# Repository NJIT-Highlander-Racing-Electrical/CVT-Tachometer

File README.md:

# CVT-Tachometer

A subsystem that measures the RPM of the primary and secondary on the CVT. This subsystem also has a temperature sensor to detect if the CVT is overheating.

## 2024-2025 Design Goals

* Everything last year seemed to work well, but a few improvements to the existing system could be made:
  * Software
       * Improve program to do more analog reads and spend less time processing data
          * This may involve constants that are only calculated once during setup, faster math functions, fewer delays, etc
       * Use the analog reads for IR sensors on both ADC1 and ADC2 to prevent any issues. 
  * Sensor Enclosures
       * the sensor housings should be made out of something other than PLA
       * they should be able to fit custom PCBs with connectors
       * the hood around the emitter and receiver should be enlarged to prevent anything else from reflecting other than what is directly in front
  * PCBs for sensors
       * the wiring from the sensors to the main electronics housing were tough to do
       * A small PCB for the electronics would be nicer than hand soldering wires
       * A connector would also be good so that they can be removed/swapped easily
            * Maybe 1x4 or 1x5 or 1x6 JST depending on how many conductors we need going to each board
  * Additional TMP36 Sensor
      * Another TMP36 temperature sensor can be added so that there is only one version of the sensor PCB, and we get a better idea of the temperature gradient within the CVT case (primary vs secondary).
  * Additional Note
     * On the IR receiver output, have it split to two GPIO. One leg has a potentiometer (0-10k?) between the output and the GPIO for finding the optimal resistance. Also make sure it has a small series resistor to prevent resistance from dropping completely to zero. The other GPIO has a fixed resistor that can be added after the fact that will be used in the long term. 

## Hardware Components:

* IR Sensors that point at primary and secondary.
- These can detect when a white stripe on the CVT passes by (one revolution)
* Microcontroller to convert the number of revolutions per second into an RPM value for dashboard and DAS (via CAN-Bus)
  - Uses ESP32 and TJA1051T CAN-Bus transceiver
* TMP36 Temperature Sensor to look at ambient temperature in the CVT case
- Sends a bit via CAN-Bus to turn on an overheating status LED on the dashboard

 ## Notes

 * Super-Bright IR LEDs support an output current of 100mA with a forward voltage of 1.6V. This means a voltage drop of 5V-1.6V = 3.4V across the 1W resistor. To achieve a current of roughly 75mA, we are using a 47 ohm resistor
    * 5V -> IR LED -> Resistor -> Ground
 * Using standard infrared photodiodes, we can simply power the IR leds without needing a 38kHz pulse rate
    * 5V -> IR Diode -> Resistor -> Ground (sample signal between diode and resistor voltage divider)
 * Temperature sensor is TMP36
    * 5V - > TMP36 VCC, GND -> TMP 36 GND, VOUT -> GPIO
 * Connections from the LEDs/sensors to the main body should be sealed/waterproof
 * The holes in the CVT case should be 20mm
 * The infrared diode appears to act like a variable resistor, but voltage polarity must be + on cathode (short negative leg) and - on anode (short positive leg)

 * The software utilizes the dual core functionality of the ESP32
   * Core 1 reads primaryRPM and deals with CAN-Bus communication
      * It is very important that all other processing is kept to a minimum to ensure primaryRPM is accurately read
   * Core 0 solely reads secondaryRPM

### Previous Issues 
 * One issue noticed during the testing phase was that the analog sensor readings were constantly peaking (4095). The resistor divider for the IR receivers needed to be adjusted to roughly 2700 ohms
 * It looked like the analog readings were having issues at comp too. It was either 0-3 ish mph or 41
     * This has been solved on 9/18/24 with dynamically adjusting analog thresholds
 * Analog reads are not ideal for this type of data acquisition. Fast readings are needed, and there should be no margin for error about whether a reading falls within a range
 * Digital readings with a hall sensor, engine spark plug with octocoupler, or some other digital signal could be implemented 

## Electrical Wiring Notes

### Pins to sensor modules

* Pin 1: +5V
* Pin 2: GND
* Pin 3: TMP36 Output
* Pin 4: IR Emitter Return Line
* Pin 5: IR Receiver Return Line

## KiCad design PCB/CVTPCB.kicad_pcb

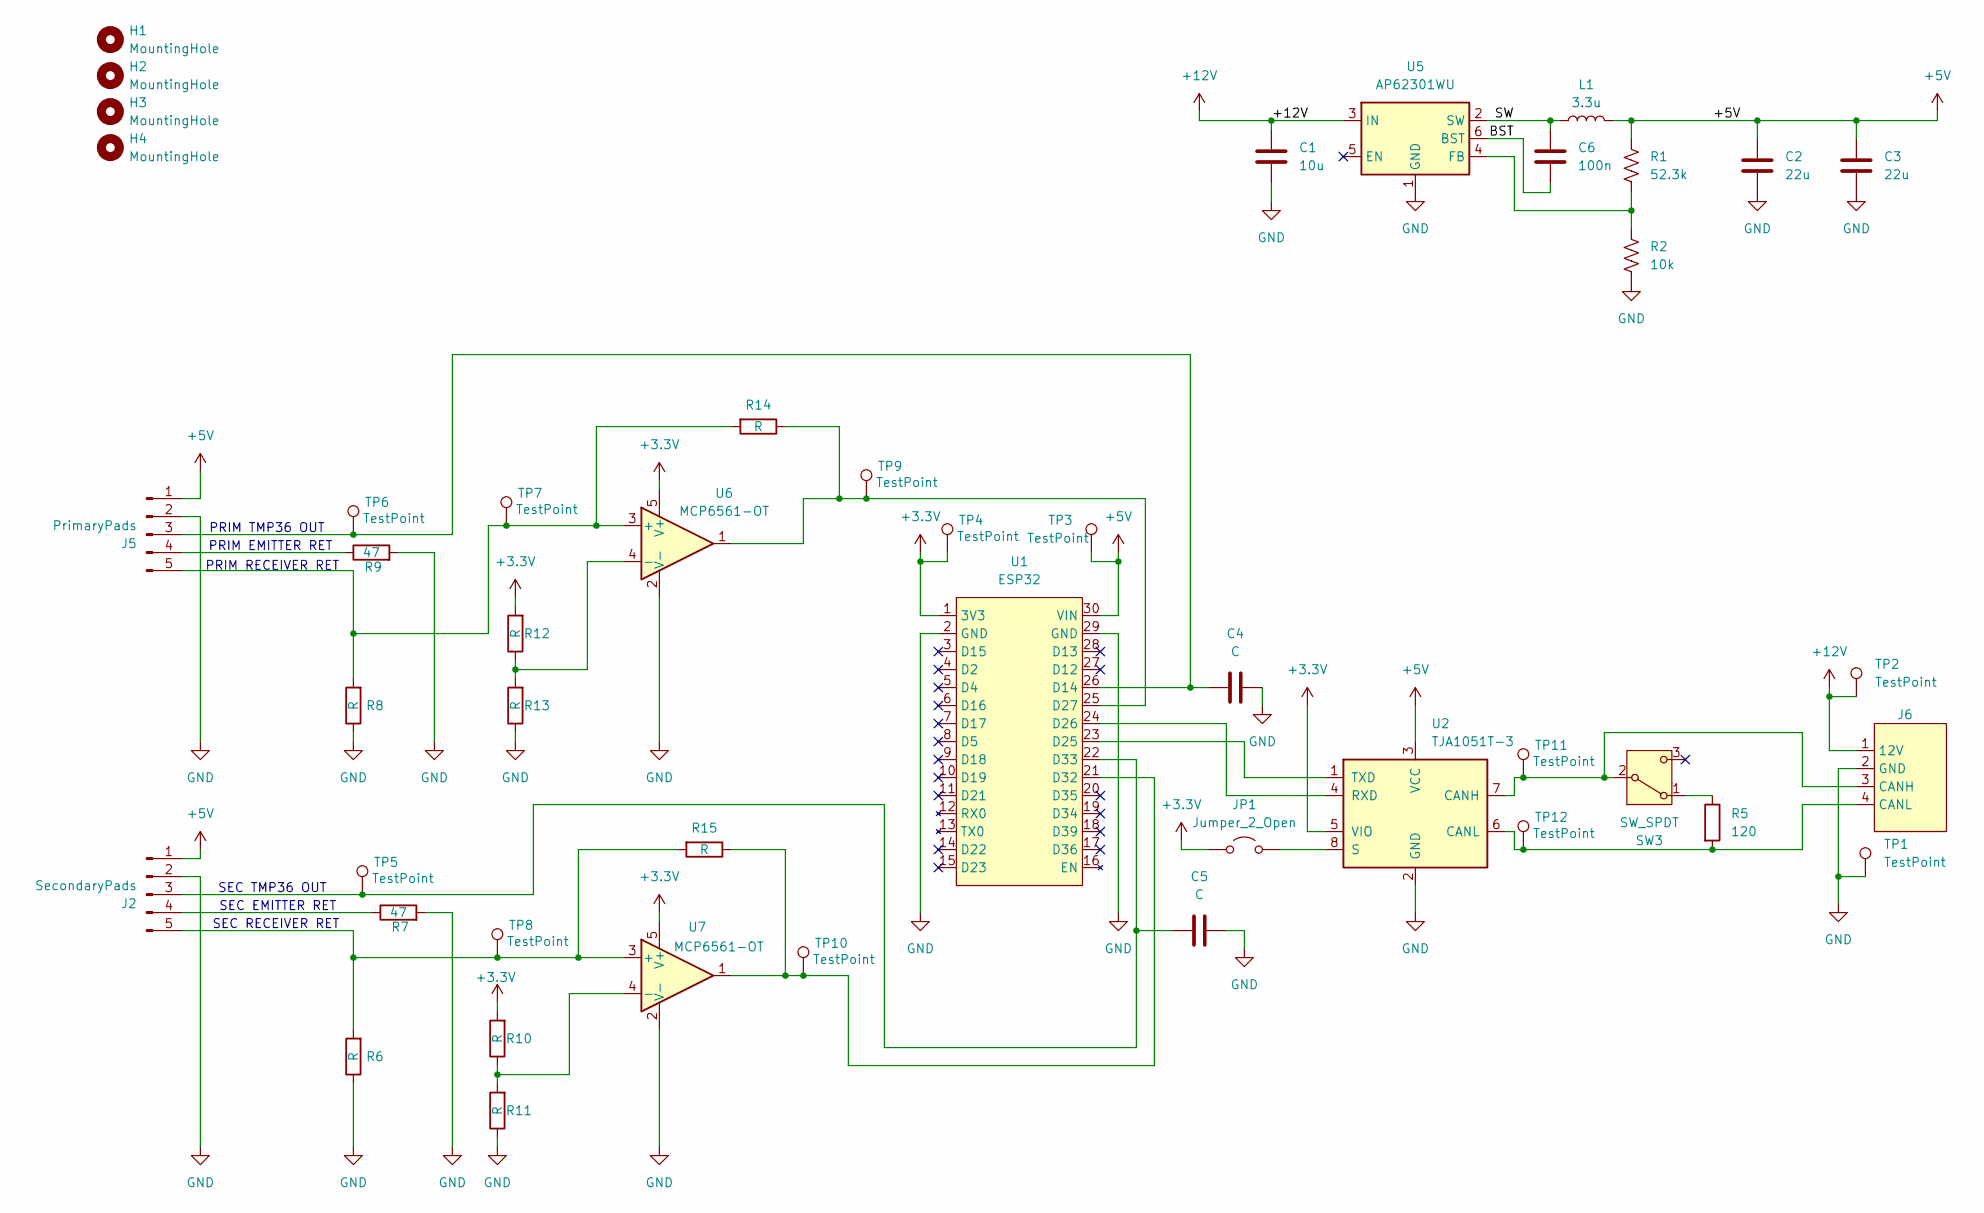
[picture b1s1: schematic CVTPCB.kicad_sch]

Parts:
C1: 10u; C_0805_2012Metric_Pad1.18x1.45mm_HandSolder
C2, C3: 22u; C_0603_1608Metric_Pad1.08x0.95mm_HandSolder
C4, C5: C; C_0805_2012Metric_Pad1.18x1.45mm_HandSolder
C6: 100n; C_0402_1005Metric_Pad0.74x0.62mm_HandSolder
H1, H2, H3, H4: MountingHole; MountingHole_4.3mm_M4
J2: SecondaryPads; Temp_IR_5_Pad_Combo
J5: PrimaryPads; Temp_IR_5_Pad_Combo
J6: Aviation Plug Pads
JP1: Jumper_2_Open; SolderJumper-2_P1.3mm_Open_Pad1.0x1.5mm
L1: 3.3u; L_Taiyo-Yuden_NR-50xx
R1: 52.3k; R_0402_1005Metric
R2: 10k; R_0402_1005Metric
R5: 120; R_1206_3216Metric_Pad1.30x1.75mm_HandSolder
R6, R8, R10, R11, R12, R13, R14, R15: R; R_1206_3216Metric_Pad1.30x1.75mm_HandSolder
R7, R9: 47; R_Axial_DIN0411_L9.9mm_D3.6mm_P12.70mm_Horizontal
SW3: SW_SPDT; SW_SPDT_CK_JS102011SAQN
TP1, TP2, TP3, TP4, TP5, TP6, TP7, TP8, TP9, TP10, TP11, TP12: TestPoint; TestPoint_THTPad_D3.0mm_Drill1.5mm
U1: ESP32
U2: TJA1051T-3; SOIC-8_3.9x4.9mm_P1.27mm
U5: AP62301WU; TSOT-23-6
U6, U7: MCP6561-OT; SOT-23-5

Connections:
+3.3V: JP1.1 (A), R10.2, R12.2, TP4.1, U1.1 (3V3), U2.5 (VIO), U6.5 (V+), U7.5 (V+)
+5V: C2.1, C3.1, J2.1, J5.1, L1.2, R1.1, TP3.1, U1.30 (VIN), U2.3 (VCC)
+12V: C1.1, J6.1 (12V), TP2.1, U5.3 (IN)
/BST: C6.2, U5.6 (BST)
/SW: C6.1, L1.1, U5.2 (SW)
GND: C1.2, C2.2, C3.2, C4.2, C5.2, J2.2, J5.2, J6.2 (GND), R2.2, R6.1, R7.2, R8.1, R9.2, R11.1, R13.1, TP1.1, U1.2 (GND), U1.29 (GND), U2.2 (GND), U5.1 (GND), U6.2 (V-), U7.2 (V-)
unnamed: C5.1, J2.3, TP5.1, U1.22 (D33)
unnamed: J2.4, R7.1
unnamed: J2.5, R6.2, R15.2, TP8.1, U7.3 (+)
unnamed: C4.1, J5.3, TP6.1, U1.26 (D14)
unnamed: J5.4, R9.1
unnamed: J5.5, R8.2, R14.2, TP7.1, U6.3 (+)
unnamed: J6.3 (CANH), SW3.2 (B), TP11.1, U2.7 (CANH)
unnamed: J6.4 (CANL), R5.2, TP12.1, U2.6 (CANL)
unnamed: JP1.2 (B), U2.8 (S)
unnamed: R5.1, SW3.1 (A)
unnamed: U1.23 (D25), U2.1 (TXD)
unnamed: U1.24 (D26), U2.4 (RXD)
unnamed: R14.1, TP9.1, U1.25 (D27), U6.1
unnamed: R15.1, TP10.1, U1.21 (D32), U7.1
unnamed: R1.2, R2.1, U5.4 (FB)
unnamed: R12.1, R13.2, U6.4 (-)
unnamed: R10.1, R11.2, U7.4 (-)

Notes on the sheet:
PRIM TMP36 OUT
SEC RECEIVER RET
SEC EMITTER RET
PRIM EMITTER RET
PRIM RECEIVER RET
SEC TMP36 OUT

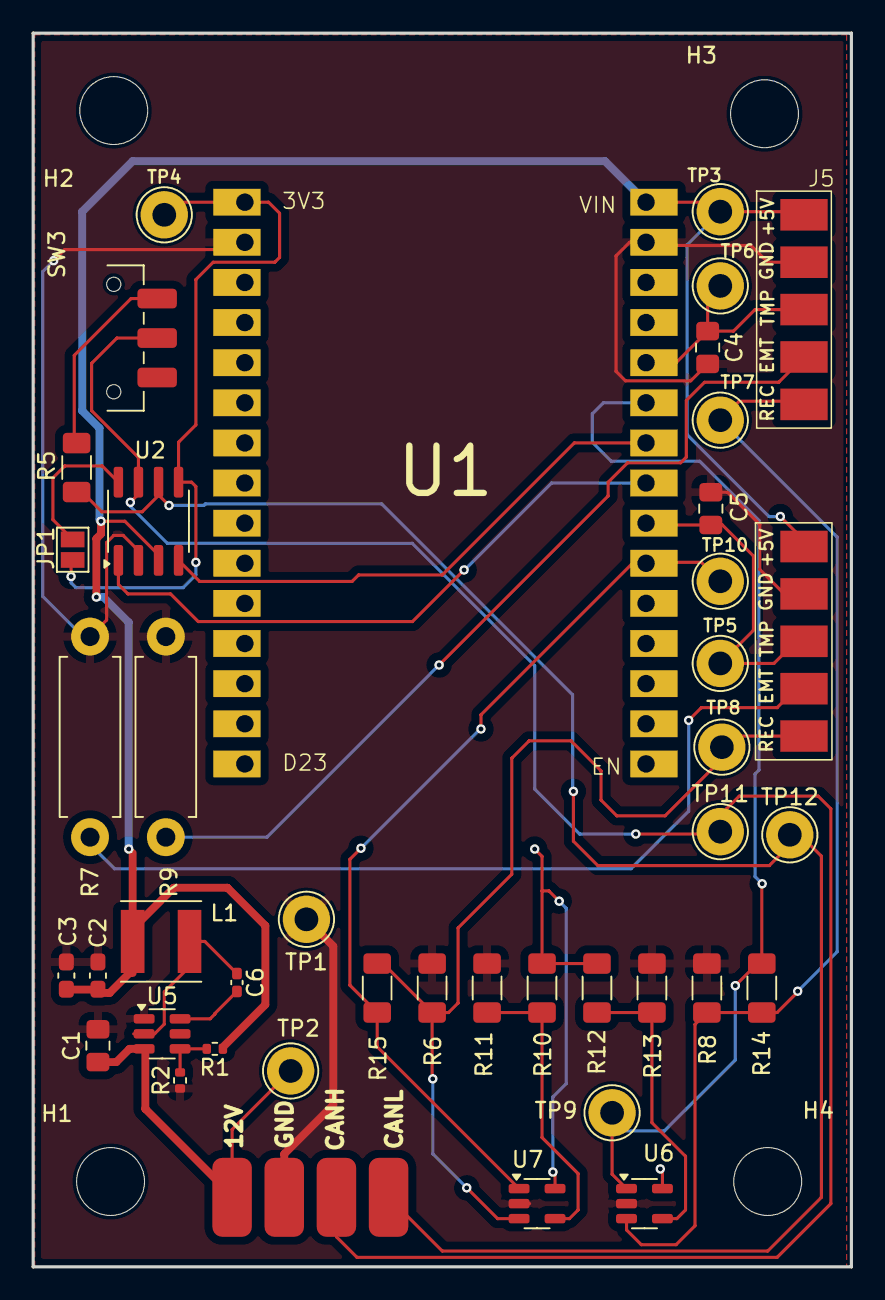
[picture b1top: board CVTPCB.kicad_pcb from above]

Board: 2 copper layers, 51.8 x 78.1 mm, 46 parts (0 on the bottom side), 23 nets.

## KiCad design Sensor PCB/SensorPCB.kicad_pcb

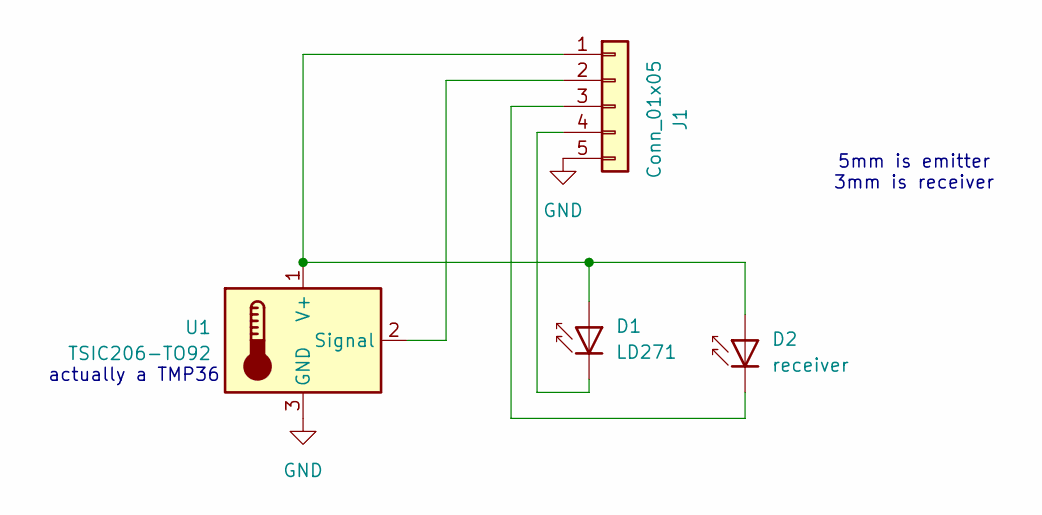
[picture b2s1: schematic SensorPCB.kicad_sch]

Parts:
D1: LD271; LED_D5.0mm_IRGrey
D2: receiver; LED_D3.0mm_IRBlack
J1: Conn_01x05; JST_EH_B5B-EH-A_1x05_P2.50mm_Vertical
U1: TSIC206-TO92; TO-92_Inline

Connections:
GND: J1.5, U1.3 (GND)
unnamed: D1.2 (A), D2.2 (A), J1.1, U1.1 (V+)
unnamed: D1.1 (K), J1.4
unnamed: D2.1 (K), J1.3
unnamed: J1.2, U1.2 (Signal)

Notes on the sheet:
5mm is emitter 3mm is receiver
actually a TMP36

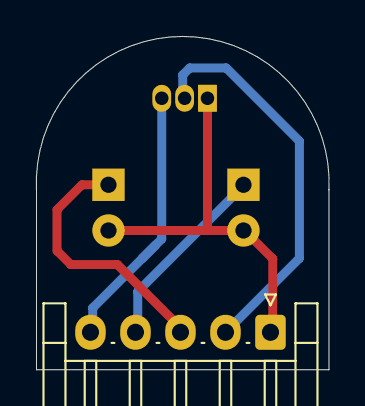
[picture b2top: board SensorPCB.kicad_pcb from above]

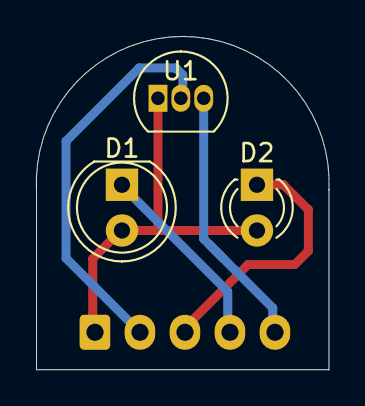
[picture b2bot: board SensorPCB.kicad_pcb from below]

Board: 2 copper layers, 16.3 x 18.5 mm, 4 parts (3 on the bottom side), 5 nets.

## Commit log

2023-10-14 Create MicrocontrollerSoftware.ino
    Began writing the code (DOES NOT BUILD)
2023-10-15 Rename BOM.txt to BOM.md
2023-12-02 12/2
    Fixed issues causing build to fail.
    Still need to test.
2024-03-13 Create test
2024-03-13 Rename 3D Models/CVT Infrared Sensors Main Body (No Temperature Sensor).stl to 3D Models/OldDesigns/CVT Infrared Sensors Main Body (No Temperature Sensor).stl
2024-03-13 Rename 3D Models/CVT Infrared Sensors Main Body (With Temperature Sensor).stl to 3D Models/OldDesigns/CVT Infrared Sensors Main Body (With Temperature Sensor).stl
2024-03-13 Rename 3D Models/CVT Infrared Sensors Nut.stl to 3D Models/OldDesigns/CVT Infrared Sensors Nut.stl
2024-04-11 Rename MicrocontrollerSoftware/MicrocontrollerSoftware.ino to MicrocontrollerSoftware/Archive/MicrocontrollerSoftware.ino
2024-04-11 Rename MicrocontrollerSoftware/Tachometer.cpp to MicrocontrollerSoftware/Archive/Tachometer.cpp
2024-04-11 Rename MicrocontrollerSoftware/Tachometer.h to MicrocontrollerSoftware/Archive/Tachometer.h
2024-04-19 4/19
2024-04-19 Fixed Git
2024-04-21 Rename IMG_0788.JPEG to Photos/IMG_0788.JPEG
2024-05-14 moving 2023-2024 files to archive
2024-05-14 adding default files and folders
2024-09-14 Update MainCode.ino
    Add global variables for dynamic trigger threshold
2024-09-14 Update secondary threshold calculations
2024-09-14 Update primary threshold calculations
2024-09-19 General Description Updates
2024-09-19 Major overhaul to program
    Add dynamically adjusting thresholds based on min/max readings
    Replace single midpoint threshold with lower 1/3 and upper 1/3 threshold for more reliable readings
    Modify Serial Prints to work with Plotter
    NOTE: averaging should be used with a timeout for smoother readings
2024-10-18 Update debug prints and add RPM zeroing timeout
2024-10-18 Create Library123
2024-10-20 Update Software Folder Layout
2024-11-14 Rename 3D Models/CVTMain v2.step to 3D Models/Alternative Designs/CVTMain v2.step
2024-11-15 Update Enclosure Model
2024-11-17 Update Enclosure
2024-11-21 Various changes to PCB design
    Changes:
    Move 4 pin aviation plug connector to bottom of PCB
    Move 0.1uF bypass capacitors from Vout to Vs
    Remove voltage divider on TMP36 output. TMP36 output ranges from 0.1V to 2.0V, which is within our 0-3.3V reading range on ESP32
    Change signal voltage divider for IR receiver from 1W footprint to 1/4W footprint
    Combine +5V and GND pads for IR and TMP36
2024-11-21 Fix missing silkscreen and flipped orientation of pot
2024-11-21 Fix reversed silkscreen markings
2024-11-21 probably finish sensor pcb
2024-11-23 Update PCB to have JST on Back side and add DRL Files
2024-11-24 Last four commits are just me deleting old GBR/DRL files and uploading the latest
2024-11-24 Fix issue where plane was extending beyond cut line
2024-12-05 Partial fix for incorrect voltage divider
2024-12-05 Add first version of code
2024-12-05 Complete pot/resistor issue fix
2024-12-05 Update enclosure to work with new PCB design fix
2024-12-07 Add latest GBR/DRL Files
2024-12-07 Remove old GBR/DRL Files
2024-12-27 Add warning about analog inputs exceeding 3.3V
2024-12-29 Update 3D Models
2025-01-06 Fix issue where watchdog being triggered on core 0
    This issue seemed to stem from the size of the stack for the task. It was set to 10000, and I set it down to 1000. This cause guru meditation errors with stack overflow, so I bumped it back up to 200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
2025-01-07 Autoformat + Add CAN send intervals
2025-01-07 Add "Ignore Readings" Code
    This code is meant to ignore any calculations that may happen after a long task, such as printing to the serial monitor or sending CAN data. Since we are not actively monitoring the analog reads duri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
2025-01-07 Fix syntax issue in previous commit
2025-01-07 Add basic status reporting software
2025-01-07 Add checkForRTR and checkStatus functions
2025-01-07 Implement Several Bug Fixes
    Fix issue where packetId was not checked during RTR reception
    Increase baud rate to fix any issues associated with serial prints
    Remove statusCVT print from general sendCAN function; this should only occur upon request
2025-01-07 Remove serial print from RTR send
2025-01-08 Change temperature status conditions
2025-01-08 Update documentation
2025-01-10 Fix bug in readSecondary where if else statements were not executing correctly
2025-02-12 Temporary Fix for data not updating
    I set the ignoreReadings to false because my hand can only go so fast. However, this presents another issue for the car. If we are only getting something like three revolutions per second, we will ne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
2025-02-15 Remove ignore reading code
    Although the serial printing takes ~7000us, it is not worth having ignore reading code. If the readings are too slow (fewer readings per second than instances of printing to serial monitor), then we 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
2025-02-15 Decrease stability delay, not sure if necessary
2025-02-15 Put delay back to 1ms because of watchdog timer
2025-03-29 Add small calibration offset to primary temperature sensor
    It reads 65 degrees in a room that is 75 degrees. I think this is just because the voltage that the module is getting is slightly lower/higher than it should be, so this accounts for that.
2025-03-29 Add secondary temp offset too
2025-03-29 Update to latest CAN Software
2025-04-02 Update CAN Frequency to 1000kbit/s
2025-04-02 FIx ESP32JSA1000 prescale register write
    This fix should eliminate the issue where setting the CAN baud rate actually sets it to half that value
2025-04-02 Maintain serial print speed at 460800
2025-04-02 Update CAN
2025-04-12 Fix Noisy Temperature Sensor Readings
    Not entirely successful, but helps noise on temperature sensor readings a bit. Just averages 10 readings before calculating
2025-04-24 Add version for READING READING MATH instead of READING MATH READING
    This is for if we have 5+ alternating dark/light spots on the CVT. At max RPM, it would be too slow to calculate the RPM every time we get a new reading. We can get away with just waiting for two con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
2025-05-01 Switch to fixed resistors, increase debug print interval
2025-05-01 Add delay only when CAN sends to allow watchdog to reset on secondary core
2025-05-01 Fix bounds
2025-05-02 Several updates, see desc
    Group all user defined parameters together
    Add variables for number of targets on CVT (since primary has two)
    Update primaryRPM and secondaryRPM calculations to include these target variables
2025-05-10 Several updates
    I think the status bits / RTRs may have been causing issues, so those are removed.
    In the case that extremely long CAN messages (like sending 250000 RPM) are causing the issues on startup (when the CVT sensors have not been calibrated), I added a statement that first checks if the 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
2025-05-10 Remove temp prints
2025-05-10 Reduce time between serial prints (see explanation)
    Although keeping the serial print frequency lower helps to have more analog reads, you can't even see what's happening. So for debugging purposes, a higher frequency is slightly less accurate but bet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
2025-05-10 Working code
2025-05-10 Turn off serial printing
2025-05-11 revert to 500kpbs
2025-06-14 Fix primary temperature offset
2025-07-05 See description
    Untested code, adds some features for better accuracy when sampling. Now, ADC takes five samples of the IR pin and averages before using primaryValue and secondaryValue in calculations.
    abs was added to the threshold checker. This probably won't make a difference, but makes the code slightly more robust against weird errors and also easier to understand/read
    ignoreNextReading was added to the secondary code. Especially with the new averaging, sending data to the CAN bus and delaying 1ms for the watchdog could be enough to miss or just get the edge of a s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
2025-07-25 Several Updates
    Increase number of samples for multisampling
    Added large decoupling caps to power pins
    Added small decoupling caps to analog input pins
    Added exponential growth and decay instead of regular min/max for creating bounds
    Added small microseconds delay between analogreadings for IR when averaging
2025-09-06 Can't update to 2.0.0 but increase speed
2025-09-06 Fix printing
2025-09-06 Change CVT temp readings to ints instead of floats. See description
    This float sending doesnt work with the latest 2.0.0 can driver that everything else uses. We really don't need decimal precision anyway, so until tihs subsystem is updated to use all interrupts and 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
2025-09-08 Update to new PCB
    This PCB features comparators with hysteresis added, surface mount hardware for voltage regulation and CAN protocol, and numerous test points for debugging
2025-09-27 Update PCB to use comparator, includes new GBR and DRL
2025-09-27 Dunno
2025-10-11 (MAJOR) Update CVT program to use comparator readings
    Applicable to '25 car revamped board and will also be used on '26 car
2025-10-11 Add code to account for possibility of outlandish double readings
2025-10-24 Update CVT Program
2025-10-24 update num targets
2025-10-24 It works
2026-04-26 Add MLX90640 hot spot reading to replace MLX90614 belt temp sensor
